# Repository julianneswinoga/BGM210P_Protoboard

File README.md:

# BGM210P_Protoboard
Breakout board for the [BGM210P Bluetooth 5.1 Module](https://www.silabs.com/documents/public/data-sheets/bgm210p-datasheet.pdf)

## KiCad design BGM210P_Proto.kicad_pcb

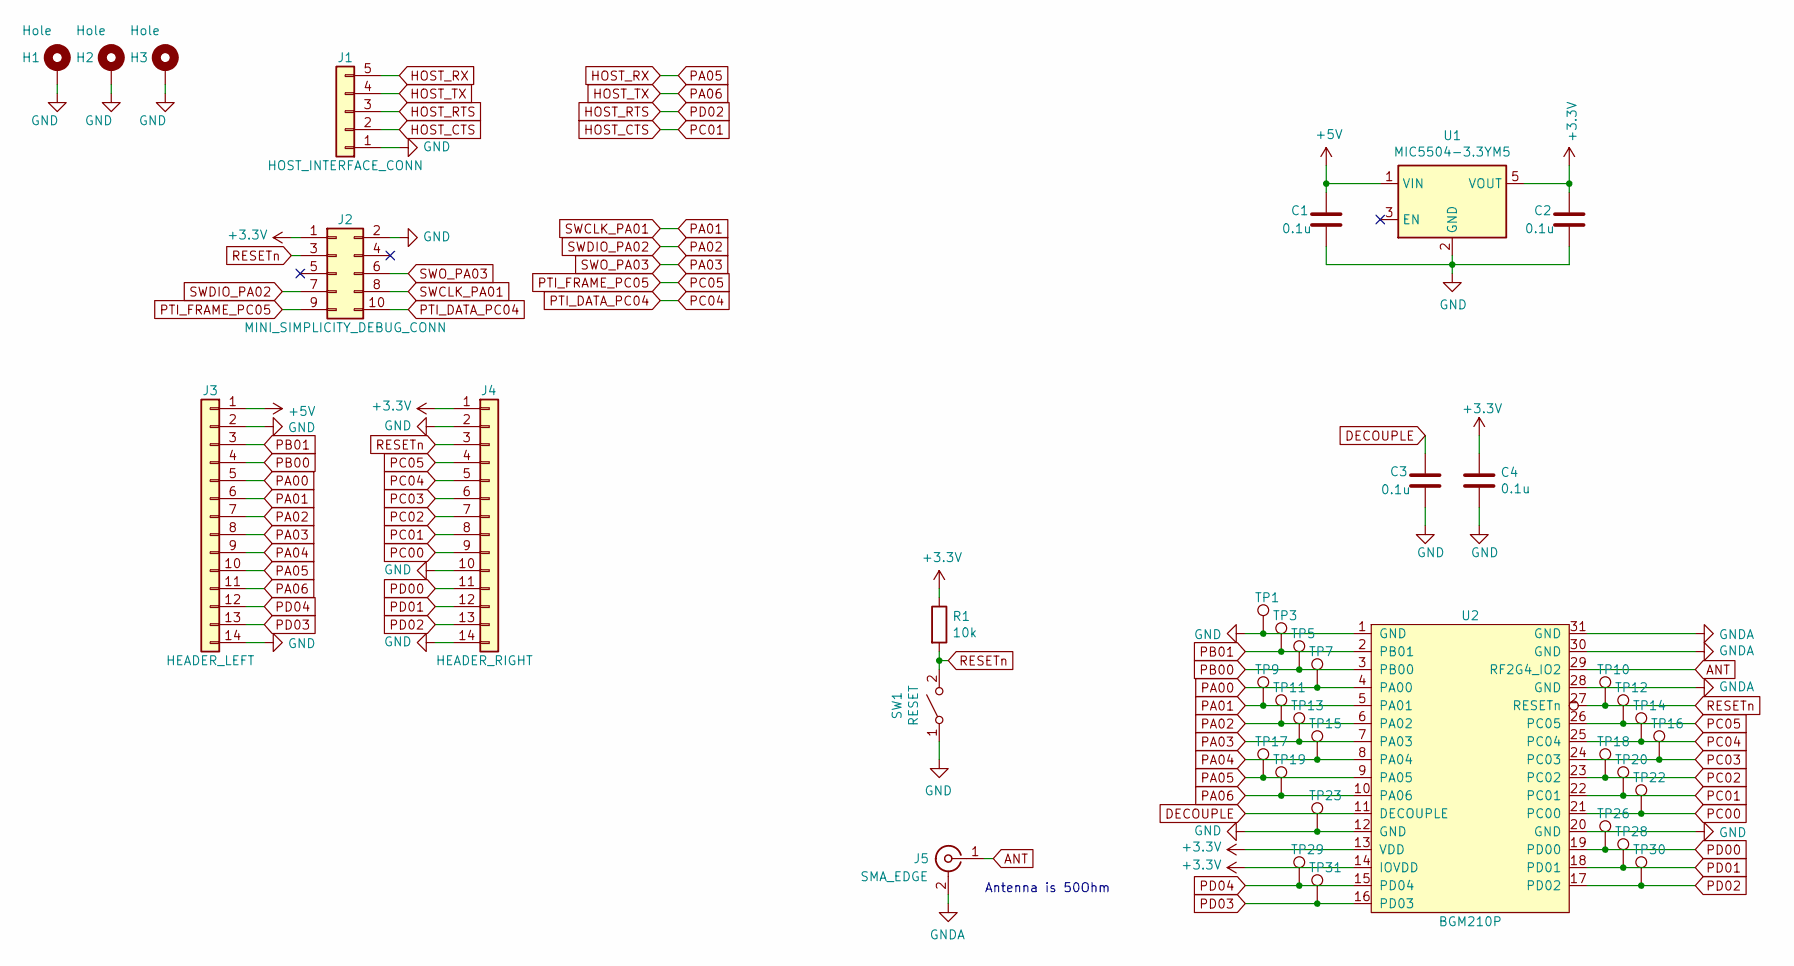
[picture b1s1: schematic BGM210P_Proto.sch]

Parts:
C1, C2, C3, C4: 0.1u; C_0603_1608Metric
H1, H2, H3: Hole; MountingHole_3.2mm_M3_Pad_Via
J1: HOST_INTERFACE_CONN; PinHeader_1x05_P2.54mm_Vertical
J2: MINI_SIMPLICITY_DEBUG_CONN; PinHeader_2x05_P1.27mm_Vertical
J3: HEADER_LEFT; PinHeader_1x14_P2.54mm_Vertical
J4: HEADER_RIGHT; PinHeader_1x14_P2.54mm_Vertical
J5: SMA_EDGE; SMA_Amphenol_132289_EdgeMount
R1: 10k; R_0603_1608Metric
SW1: RESET; SW_SPST_PTS645
TP1, TP3, TP5, TP7, TP9, TP10, TP11, TP12, TP13, TP14, TP15, TP16, TP17, TP18, TP19, TP20, TP22, TP23, TP26, TP28, TP29, TP30, TP31: TestPoint_Pad_1.0x1.0mm
U1: MIC5504-3.3YM5; SOT-23-5
U2: BGM210P; MODULE_MGM111A256V2

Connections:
+3V3: C2.1, C4.1, J2.1, J4.1, R1.1, U1.5 (VOUT), U2.13 (VDD), U2.14 (IOVDD)
+5V: C1.1, J3.1, U1.1 (VIN)
ANT: J5.1 (In), U2.29 (RF2G4_IO2)
DECOUPLE: C3.1, U2.11 (DECOUPLE)
GND: C1.2, C2.2, C3.2, C4.2, H1.1, H2.1, H3.1, J1.1, J2.2, J3.2, J3.14, J4.2, J4.10, J4.14, SW1.1 (A), TP1.1, TP23.1, U1.2 (GND), U2.1 (GND), U2.12 (GND), U2.20 (GND)
GNDA: J5.2 (Ext), U2.28 (GND), U2.30 (GND), U2.31 (GND)
HOST_CTS: J1.2, J4.8, TP20.1, U2.22 (PC01)
HOST_RTS: J1.3, J4.13, TP30.1, U2.17 (PD02)
HOST_RX: J1.5, J3.10, TP17.1, U2.9 (PA05)
HOST_TX: J1.4, J3.11, TP19.1, U2.10 (PA06)
PA00: J3.5, TP7.1, U2.4 (PA00)
PA01: J2.8, J3.6, TP9.1, U2.5 (PA01)
PA02: J2.7, J3.7, TP11.1, U2.6 (PA02)
PA03: J2.6, J3.8, TP13.1, U2.7 (PA03)
PA04: J3.9, TP15.1, U2.8 (PA04)
PB00: J3.4, TP5.1, U2.3 (PB00)
PB01: J3.3, TP3.1, U2.2 (PB01)
PC00: J4.9, TP22.1, U2.21 (PC00)
PC02: J4.7, TP18.1, U2.23 (PC02)
PC03: J4.6, TP16.1, U2.24 (PC03)
PC04: J2.10, J4.5, TP14.1, U2.25 (PC04)
PC05: J2.9, J4.4, TP12.1, U2.26 (PC05)
PD00: J4.11, TP26.1, U2.19 (PD00)
PD01: J4.12, TP28.1, U2.18 (PD01)
PD03: J3.13, TP31.1, U2.16 (PD03)
PD04: J3.12, TP29.1, U2.15 (PD04)
RESETn: J2.3, J4.3, R1.2, SW1.2 (B), TP10.1, U2.27 (RESETn)

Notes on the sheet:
Antenna is 50Ohm

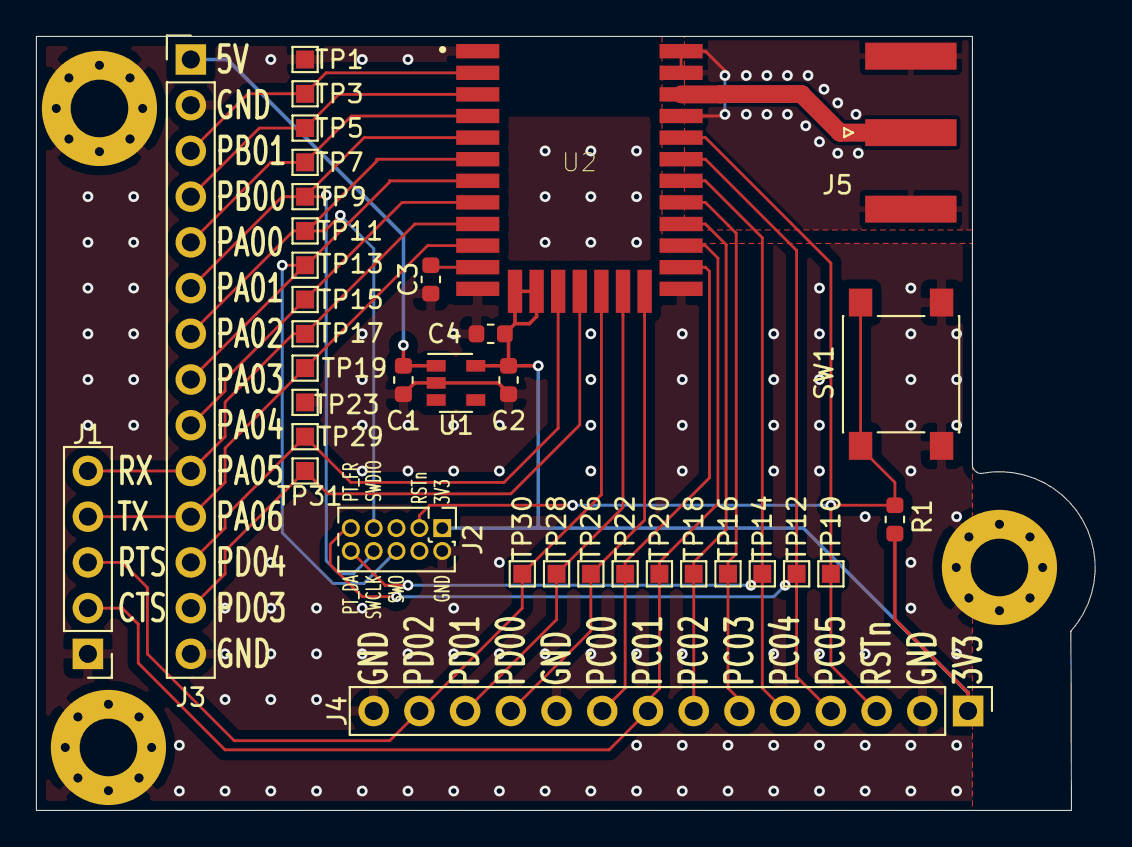
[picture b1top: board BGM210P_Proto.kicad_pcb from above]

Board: 2 copper layers, 58.8 x 43.0 mm, 39 parts (0 on the bottom side), 27 nets.

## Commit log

2020-02-13 Changed track size from 0.15 to 0.16, added silkscreen artwork , generated fab outputs
